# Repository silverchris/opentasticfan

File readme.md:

# OpentasticFan
OpentasticFan is a replacement for the factory control board found in most Fantastic Fans. It should also be possible to upgrade a basic Fantastic Fan that does not have rain sensing or power opening with the addition of a [Fantastic Fan lift motor assembly](https://www.etrailer.com/Accessories-and-Parts/Fantastic-Vent/FVK6010-80.html).

It supports:
- Cover Opening and Closing
- Rain Sensing
- Fan Speed Control 
- OLED Display and Rotary Encoder for local control
- Remote control via [Home Assistant](https://www.home-assistant.io/)

## Hardware

- [SH1106 128x64 i2c OLED Display](https://www.amazon.ca/dp/B085RYPHT2)
- [Rotary Encoder with button](https://www.amazon.ca/WayinTop-Degree-Encoder-Development-Arduino/dp/B07T3672VK/)
- [Opentasticfan PCB](hardware/2.0)
- Optional Heated Capacitive Rain Sensor

## Software
Opentasticfan uses [ESPHome](https://esphome.io). Configuration is located at [config/2.0](config/2.0).

[Example configuration](config/2.0/example.yaml)

## OpentasticFan Installed

## OpentasticFan wiring

## OpentasticFan PCB

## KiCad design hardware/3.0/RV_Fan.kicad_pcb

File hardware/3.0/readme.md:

# OpentasticFan PCB 3.0

## Updates from 2.0
- Uses ESP32-S3 instead of classic ESP32 (U5)
- USB for programming intergrated (J9, R6, R8, D1)
- Uses DRV8874PWR(U1, U2) for both motor controls. Combined with the better ADC of the ESP32-S3 gives accurate current measurement.
- AMS1117(U3) instead of switch mode regulator for power supply to reduce BOM cost
- Changed from Dallas DS18B20 to NTC thermistor(TH1) for air temperature for both the reduced cost, and due to the flaky support in ESPHome
- Added i2c pullup resistors (R1, R2)

## Assembly Notes
- ESP32-S3-WROOM-1 used, due to poor ADC on the classic ESP32. It is not availible for JLCPCB "Economic PCB Assembly" and will need to be hand soldered.
- Most SMD parts are availible through LCSC/JLCPCB with "Economic PCB Assembly". If having JLCPCB do the SMD assembly, you will need to install/solder C5, J1, J2, J3, J4, J6, J7, J8, U5
- J5 doesn't need to be populated. It's currently unused.
- Install J1, J2, so the screw terminals face out from the PCB with mating connector installed.

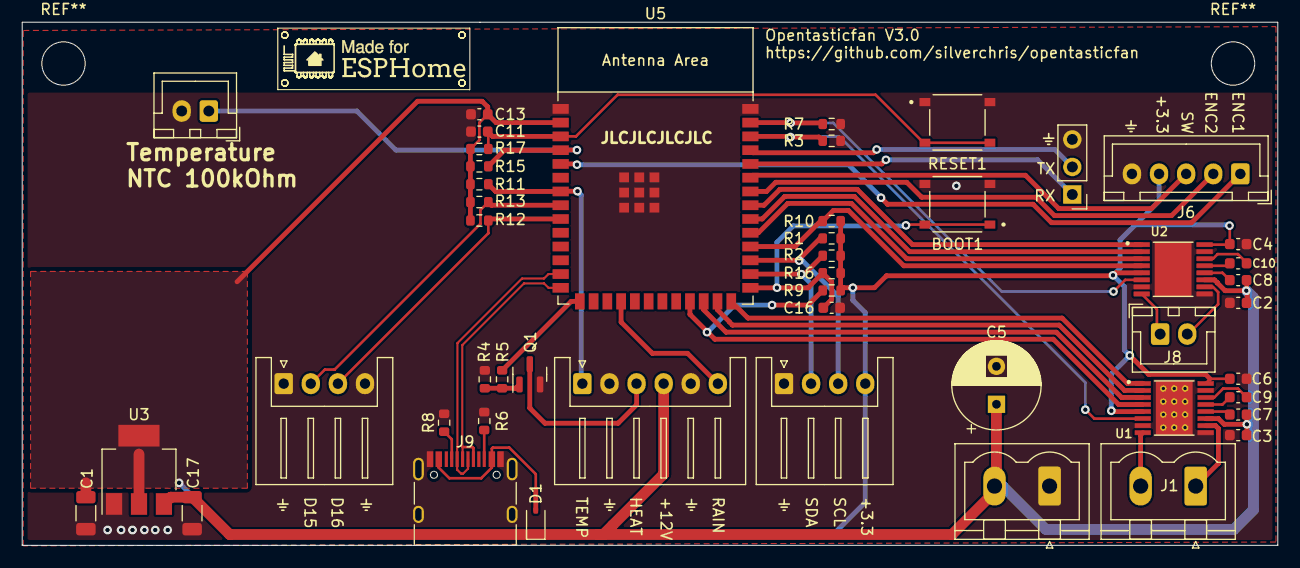
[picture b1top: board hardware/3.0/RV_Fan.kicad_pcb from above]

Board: 2 copper layers, 115.8 x 48.3 mm, 48 parts (0 on the bottom side), 45 nets.

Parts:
BOOT1: TS-1187A-B-A-B; button
C1: 22uF; C_1206_3216Metric
C2, C3, C4, C6, C7, C8, C11, C13, C16: 0.1uF; C_0603_1608Metric
C5: 220uF; CP_Radial_D8.0mm_P3.50mm
C9, C10: 22nF; C_0603_1608Metric
C17: 4.7uF; C_1206_3216Metric
D1: 1N5819WS; D_SOD-323
J1: FAN; PhoenixContact_MSTBVA_2,5_2-G-5,08_1x02_P5.08mm_Vertical
J2: PhoenixContact_MSTBVA_2,5_2-G-5,08_1x02_P5.08mm_Vertical
J3: JST_XH_S6B-XH-A_1x06_P2.50mm_Horizontal
J4, J5: JST_XH_S4B-XH-A_1x04_P2.50mm_Horizontal
J6: JST_XH_B5B-XH-A_1x05_P2.50mm_Vertical
J7: PinHeader_1x03_P2.54mm_Vertical
J8: COVER; JST_XH_B2B-XH-A_1x02_P2.50mm_Vertical
J9: USB_C_Receptacle_USB2.0; USB_C_Receptacle_HRO_TYPE-C-31-M-12
Q1: AO3400A; SOT-23
R1, R2, R4, R9, R10, R12, R13, R16, R17: 10k; R_0603_1608Metric
R3: 1.5k; R_0603_1608Metric
R5: 100; R_0603_1608Metric
R6, R8: 5.1k; R_0603_1608Metric
R7: 24k; R_0603_1608Metric
R11, R15: 51k; R_0603_1608Metric
RESET1: TS-1187A-B-A-B; button
TH1: 100k; JST_XH_B2B-XH-A_1x02_P2.50mm_Vertical
U1, U2: DRV8874PWPR; IC_DRV8876PWPT
U3: AMS1117-3.3; SOT-223-3_TabPin2
U5: ESP32-S3-WROOM-1

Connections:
+3.3V: C1.1, C4.1, C6.1, C13.1, J4.4, J6.4, R1.1, R2.1, R9.1, R10.1, R11.1, R12.1, R13.1, R15.1, R16.1, R17.1, U1.5 (VREF), U1.16 (PMODE), U2.5 (VREF), U2.16 (PMODE), U3.2 (VO), U5.2 (3V3)
+12V: C2.1, C3.1, C5.1, C7.1, C8.1, C17.1, D1.1 (K), J2.2, J3.4, U1.11 (VM), U2.11 (VM), U3.3 (VI)
/BOOT: BOOT1.1, C16.1, R16.2, U5.27 (GPIO0/BOOT)
/DEW_HEATER: R5.2, U5.15 (GPIO3/TOUCH3/ADC1_CH2)
/DEW_HEATER_OUT: J3.3, Q1.3 (D)
/DEW_TEMP: J3.1, R11.2, U5.7 (GPIO7/TOUCH7/ADC1_CH6)
/D_IN1: J5.3, R12.2, U5.9 (GPIO16/U0CTS/ADC2_CH5/XTAL_32K_N)
/D_IN2: J5.2, R13.2, U5.8 (GPIO15/U0RTS/ADC2_CH4/XTAL_32K_P)
/EN: C11.1, R17.2, RESET1.2, U5.3 (EN)
/ENC1: J6.1, U5.5 (GPIO5/TOUCH5/ADC1_CH4)
/ENC2: J6.2, U5.34 (MTDI/GPIO41/CLK_OUT1)
/RAIN: J3.6, U5.18 (GPIO10/TOUCH10/ADC1_CH9/FSPICS0/FSPIIO4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)
/RX: J7.1, U5.36 (U0RXD/GPIO44/CLK_OUT2)
/SCL: J4.3, R1.2, U5.29 (SPIIO7/GPIO36/FSPICLK/SUBSPICLK)
/SDA: J4.2, R2.2, U5.28 (SPIIO6/GPIO35/FSPID/SUBSPID)
/SW: J6.3, U5.35 (MTMS/GPIO42)
/TEMP: R15.2, TH1.1, U5.4 (GPIO4/TOUCH4/ADC1_CH3)
/TX: J7.2, U5.37 (U0TXD/GPIO43/CLK_OUT1)
/USB_D+: J9.A6 (D+), J9.B6 (D+), U5.14 (GPIO20/U1CTS/ADC2_CH9/CLK_OUT1/USB_D+)
/USB_D-: J9.A7 (D-), J9.B7 (D-), U5.13 (GPIO19/U1RTS/ADC2_CH8/CLK_OUT2/USB_D-)
/USB_VBUS: D1.2 (A), J9.A4 (VBUS), J9.A9 (VBUS), J9.B4 (VBUS), J9.B9 (VBUS)
GND: BOOT1.2, C1.2, C2.2, C3.2, C4.2, C5.2, C6.2, C11.2, C13.2, C16.2, C17.2, J2.1, J3.2, J3.5, J4.1, J5.1, J5.4, J6.5, J7.3, J9.A1 (GND), J9.A12 (GND), J9.B1 (GND), J9.B12 (GND), J9.S1 (SHIELD), Q1.2 (S), R3.2, R4.2, R6.2, R7.2, R8.2, RESET1.1, TH1.2, U1.7 (IMODE), U1.9 (PGND), U1.15 (GND), U1.17 (EXP), U1.18 (EXP), U1.19 (EXP), U1.20 (EXP), U1.21 (EXP), U1.22 (EXP), U1.23 (EXP), U1.24 (EXP), U1.25 (EXP), U1.26 (EXP), U1.27 (EXP), U1.28 (EXP), U1.29 (EXP), U2.7 (IMODE), U2.9 (PGND), U2.15 (GND), U2.17 (EXP), U3.1 (GND), U5.1 (GND), U5.40 (GND), U5.41 (GND)
unnamed: J1.1, U1.10 (OUT2)
unnamed: J1.2, U1.8 (OUT1)
unnamed: J8.1, U2.8 (OUT1)
unnamed: J8.2, U2.10 (OUT2)
unnamed: J9.A5 (CC1), R8.1
unnamed: J9.B5 (CC2), R6.1
unnamed: Q1.1 (G), R4.1, R5.1
unnamed: C9.1, U1.13 (CPH)
unnamed: C9.2, U1.14 (CPL)
unnamed: C7.2, U1.12 (VCP)
unnamed: C10.1, U2.13 (CPH)
unnamed: C10.2, U2.14 (CPL)
unnamed: C8.2, U2.12 (VCP)
U1_IN1: U1.1 (EN/IN1), U5.26 (GPIO45)
U1_IN2: U1.2 (PH/IN2), U5.25 (GPIO48/SPICLK_N/SUBSPICLK_N_DIFF)
U1_Isense: R3.1, U1.6 (IPROPI), U5.38 (GPIO2/TOUCH2/ADC1_CH1)
U2_IN1: U2.1 (EN/IN1), U5.33 (MTDO/GPIO40/CLK_OUT2)
U2_IN2: U2.2 (PH/IN2), U5.32 (MTCK/GPIO39/CLK_OUT3/SUBSPICS1)
U2_Isense: R7.1, U2.6 (IPROPI), U5.39 (GPIO1/TOUCH1/ADC1_CH0)
~U1_FAULT: R9.2, U1.4 (~NFAULT), U5.23 (GPIO21)
~U1_SLEEP: U1.3 (NSLEEP), U5.24 (GPIO47/SPICLK_P/SUBSPICLK_P_DIFF)
~U2_FAULT: R10.2, U2.4 (~NFAULT), U5.30 (SPIDQS/GPIO37/FSPIQ/SUBSPIQ)
~U2_SLEEP: U2.3 (NSLEEP), U5.31 (GPIO38/FSPIWP/SUBSPIWP)

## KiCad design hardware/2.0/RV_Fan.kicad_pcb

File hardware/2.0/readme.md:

# OpentasticFan PCB

## Assembly Notes
- ESP32-SOLO-1 used on prototypes, for reduced JLCPCB assembly costs.
- All SMD parts are availible through LCSC/JLCPCB with "Economic PCB Assembly". If having JLCPCB do the SMD assembly, you will need to install/solder C5, U5, J1, J2, J3, J4, J6, J10
- If using a NTC thermistor instead of a DS18B20, change R15 to correct value for thermistor
- Recommend using JST XH headers for J3, J4, J6. They fit on this revision, but tightly.
- J5 doesn't need to be populated. It's currently unused.
- Install J1, J2, J10 so the screw terminals face out from the PCB with mating connector installed.

## Future Design changes
- Use ams1117 instead of switch mode regulator to reduce BOM costs/simplify.
- Replace .1" Headers with JST Connectors, for vibration resistance.
- Possibly replace DRV8874 with A4950E. This will likely result in needing to use a op-amp/current sense amplifier to monitor fan current?

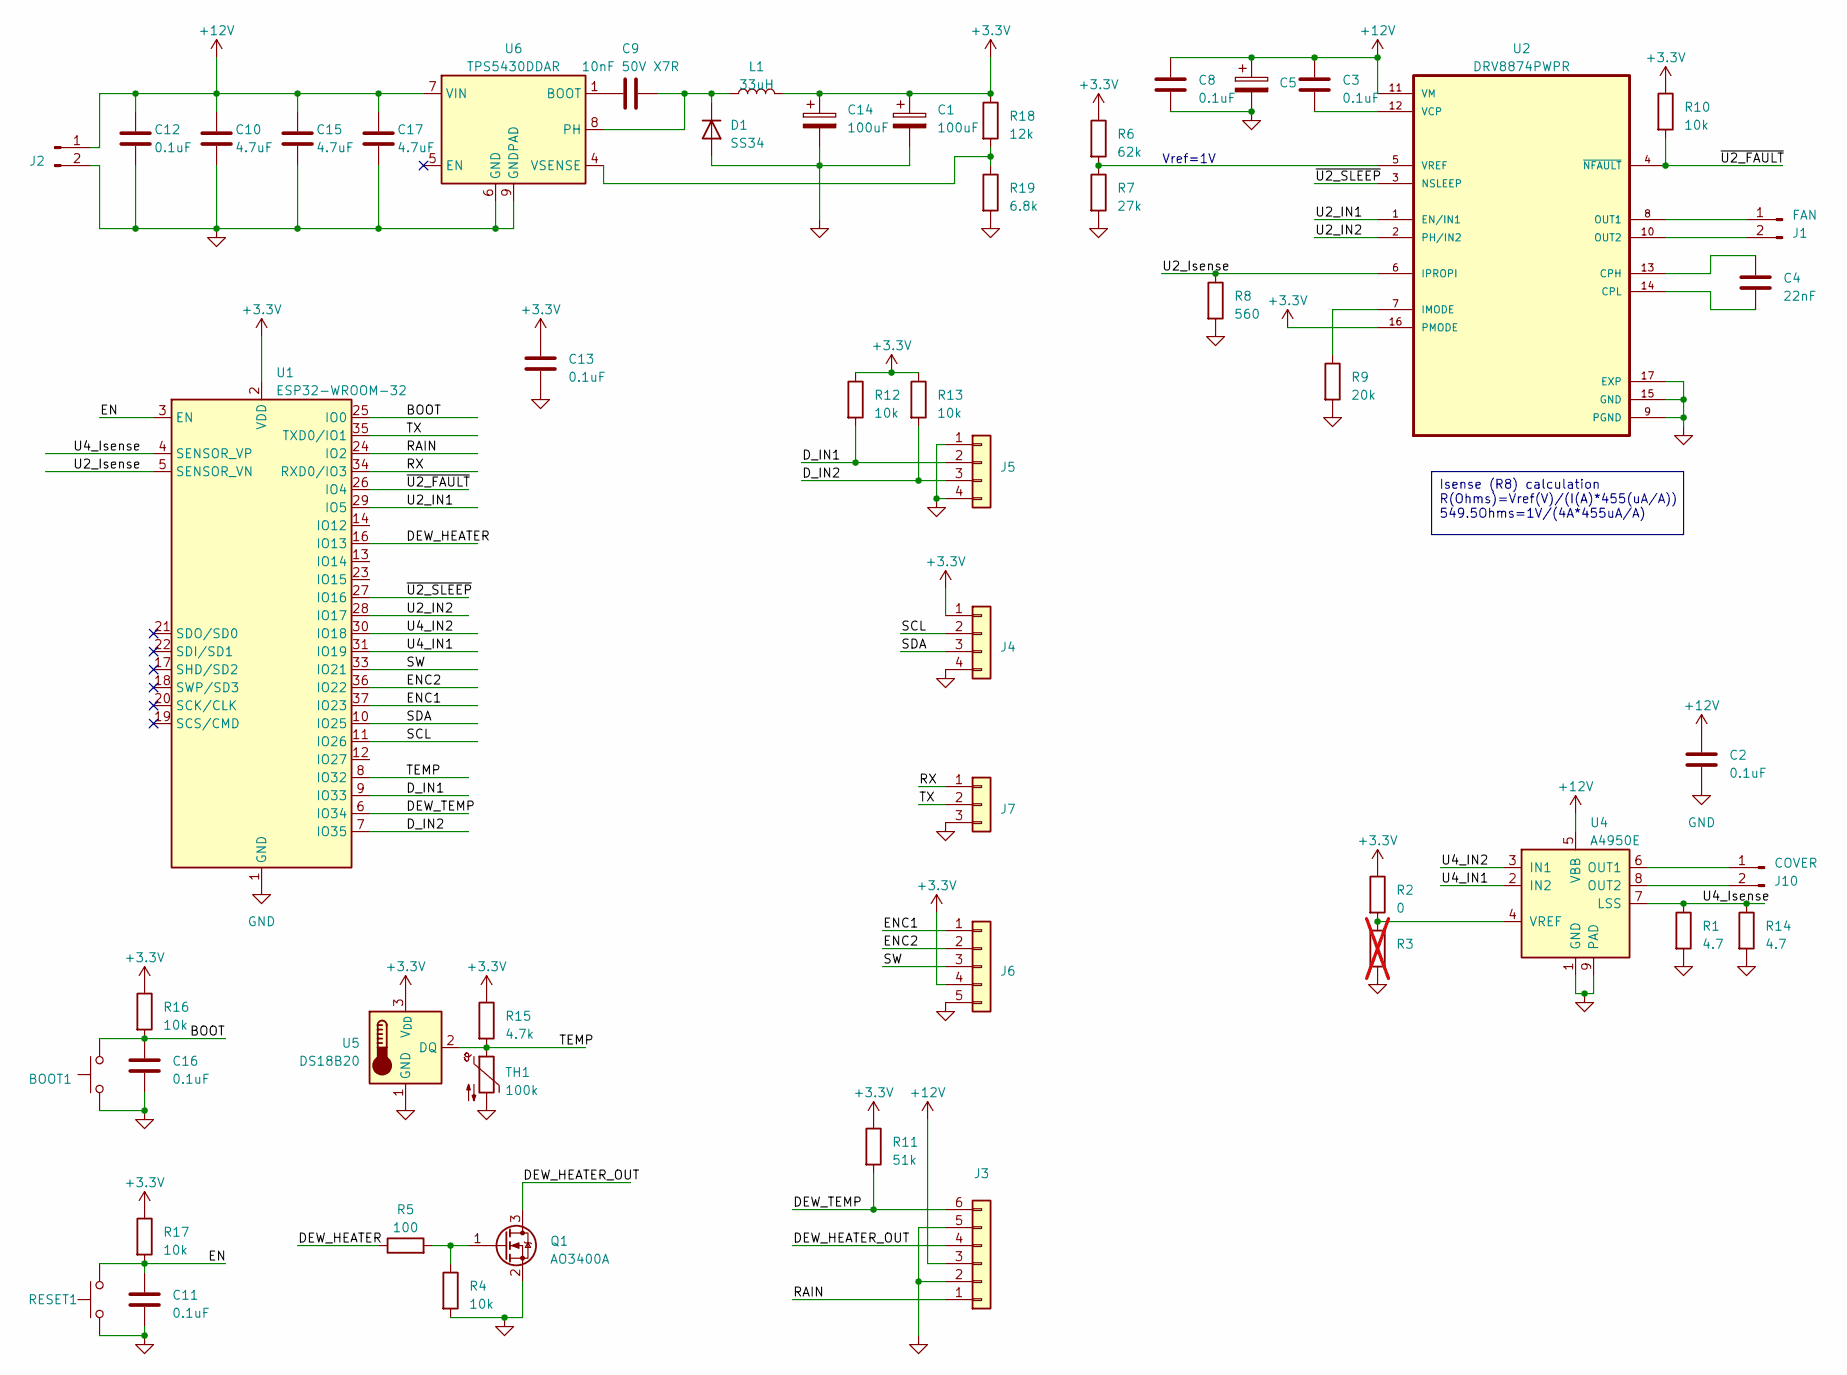
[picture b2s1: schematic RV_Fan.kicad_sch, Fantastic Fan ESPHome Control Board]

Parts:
BOOT1: TS-1187A-B-A-B; button
C1: 100uF; C_1206_3216Metric
C2, C3, C8, C11, C12, C13, C16: 0.1uF; C_0603_1608Metric
C4: 22nF; C_0603_1608Metric; LCSC Part # C21122
C5: CP_Radial_D8.0mm_P3.50mm
C9: 10nF 50V X7R; C_0603_1608Metric
C10, C15, C17: 4.7uF; C_1206_3216Metric; LCSC Part # C29823
C14: 100uF; C_1206_3216Metric; LCSC Part # C15008
D1: SS34; D_SMA
J1: FAN; PhoenixContact_MSTBVA_2,5_2-G-5,08_1x02_P5.08mm_Vertical
J2: PhoenixContact_MSTBVA_2,5_2-G-5,08_1x02_P5.08mm_Vertical
J3: PinHeader_1x06_P2.54mm_Horizontal
J4, J5: PinHeader_1x04_P2.54mm_Horizontal
J6: PinHeader_1x05_P2.54mm_Vertical
J7: PinHeader_1x03_P2.54mm_Vertical
J10: COVER; PhoenixContact_MSTBVA_2,5_2-G-5,08_1x02_P5.08mm_Vertical
L1: 33uH; 1255AY100MP3; LCSC Part # C1332315
Q1: AO3400A; SOT-23
R1, R14: 4.7; R_0805_2012Metric; LCSC Part # C17675
R2: 0; R_0603_1608Metric
R3: R_0603_1608Metric; not fitted
R4, R10, R12, R13, R16, R17: 10k; R_0603_1608Metric
R5: 100; R_0603_1608Metric
R6: 62k; R_0603_1608Metric
R7: 27k; R_0603_1608Metric
R8: 560; R_0603_1608Metric
R9: 20k; R_0603_1608Metric
R11: 51k; R_0603_1608Metric; LCSC Part # C23196
R15: 4.7k; R_0603_1608Metric
R18: 12k; R_0603_1608Metric
R19: 6.8k; R_0603_1608Metric
RESET1: TS-1187A-B-A-B; button
TH1: 100k; PinHeader_1x02_P2.54mm_Vertical
U1: ESP32-WROOM-32
U2: DRV8874PWPR; IC_DRV8876PWPT; PARTREV E; LCSC Part # C1855818
U4: A4950E; SOIC-8-1EP_3.9x4.9mm_P1.27mm_EP2.41x3.3mm
U5: DS18B20; TO-92_Inline
U6: TPS5430DDAR; TI_SO-PowerPAD-8_ThermalVias

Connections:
+3.3V: C1.1, C13.1, C14.1, J4.1, J6.4, L1.2, R2.1, R6.1, R10.1, R11.1, R12.1, R13.1, R15.1, R16.1, R17.1, R18.1, U1.2 (VDD), U2.16 (PMODE), U5.3 (V_{DD})
+12V: C2.1, C3.1, C5.1, C8.1, C10.1, C12.1, C15.1, C17.1, J2.1, J3.3, U2.11 (VM), U4.5 (VBB), U6.7 (VIN)
/BOOT: BOOT1.1, C16.1, R16.2, U1.25 (IO0)
/DEW_HEATER: R5.1, U1.16 (IO13)
/DEW_HEATER_OUT: J3.4, Q1.3 (D)
/DEW_TEMP: J3.6, R11.2, U1.6 (IO34)
/D_IN1: J5.2, R12.2, U1.9 (IO33)
/D_IN2: J5.3, R13.2, U1.7 (IO35)
/EN: C11.1, R17.2, RESET1.2, U1.3 (EN)
/ENC1: J6.1, U1.37 (IO23)
/ENC2: J6.2, U1.36 (IO22)
/RAIN: J3.1, U1.24 (IO2)
/RX: J7.1, U1.34 (RXD0/IO3)
/SCL: J4.2, U1.11 (IO26)
/SDA: J4.3, U1.10 (IO25)
/SW: J6.3, U1.33 (IO21)
/TEMP: R15.2, TH1.1, U1.8 (IO32), U5.2 (DQ)
/TX: J7.2, U1.35 (TXD0/IO1)
/U2_IN1: U1.29 (IO5), U2.1 (EN/IN1)
/U2_IN2: U1.28 (IO17), U2.2 (PH/IN2)
/U2_Isense: R8.1, U1.5 (SENSOR_VN), U2.6 (IPROPI)
/U4_IN1: U1.31 (IO19), U4.2 (IN2)
/U4_IN2: U1.30 (IO18), U4.3 (IN1)
/U4_Isense: R1.1, R14.1, U1.4 (SENSOR_VP), U4.7 (LSS)
/~U2_FAULT: R10.2, U1.26 (IO4), U2.4 (~NFAULT)
/~U2_SLEEP: U1.27 (IO16), U2.3 (NSLEEP)
GND: BOOT1.2, C1.2, C2.2, C5.2, C8.2, C10.2, C11.2, C12.2, C13.2, C14.2, C15.2, C16.2, C17.2, D1.2 (A), J2.2, J3.2, J3.5, J4.4, J5.1, J5.4, J6.5, J7.3, Q1.2 (S), R1.2, R3.2, R4.2, R7.2, R8.2, R9.2, R14.2, R19.2, RESET1.1, TH1.2, U1.1 (GND), U1.15 (GND), U1.38 (GND), U1.39 (GND), U2.9 (PGND), U2.15 (GND), U2.17 (EXP), U4.1 (GND), U4.9 (PAD), U5.1 (GND), U6.6 (GND), U6.9 (GNDPAD)
unnamed: C9.2, D1.1 (K), L1.1, U6.8 (PH)
unnamed: J1.1, U2.8 (OUT1)
unnamed: J1.2, U2.10 (OUT2)
unnamed: J10.1, U4.6 (OUT1)
unnamed: J10.2, U4.8 (OUT2)
unnamed: Q1.1 (G), R4.1, R5.2
unnamed: C4.1, U2.13 (CPH)
unnamed: C4.2, U2.14 (CPL)
unnamed: R9.1, U2.7 (IMODE)
unnamed: C3.2, U2.12 (VCP)
unnamed: R6.2, R7.1, U2.5 (VREF)
unnamed: R2.2, R3.1, U4.4 (VREF)
unnamed: C9.1, U6.1 (BOOT)
unnamed: R18.2, R19.1, U6.4 (VSENSE)

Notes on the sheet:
Isense (R8) calculation R(Ohms)=Vref(V)/(I(A)*455(uA/A)) 549.5Ohms=1V/(4A*455uA/A)
Vref=1V

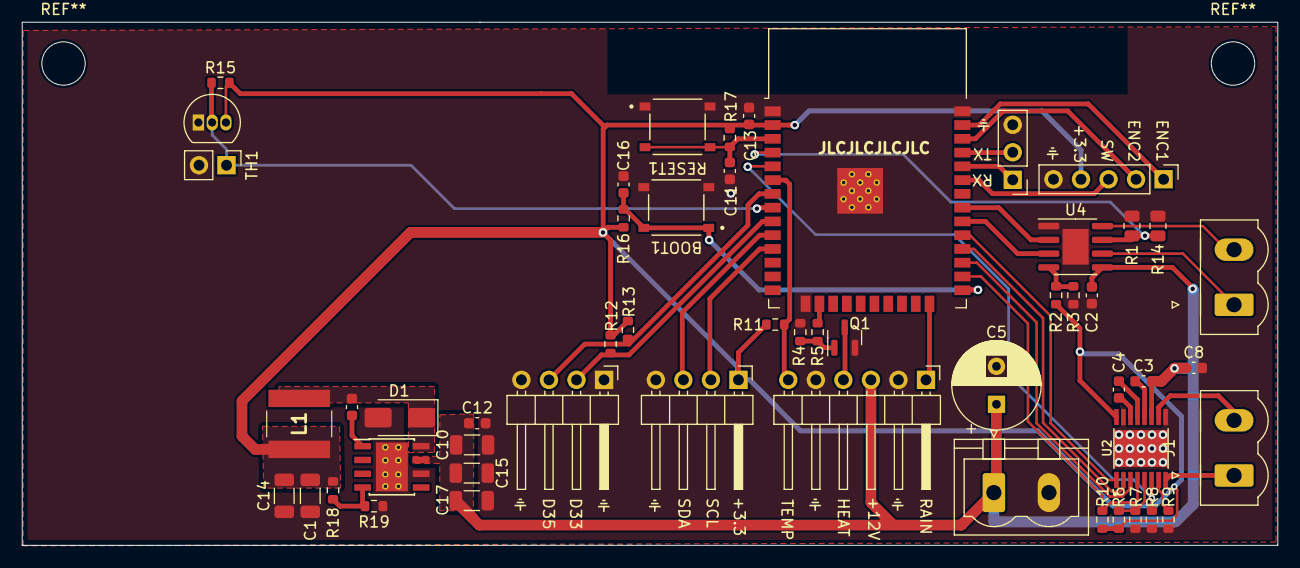
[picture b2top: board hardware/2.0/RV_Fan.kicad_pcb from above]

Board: 2 copper layers, 115.8 x 48.3 mm, 53 parts (0 on the bottom side), 41 nets.

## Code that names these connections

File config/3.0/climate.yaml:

substitutions:
  temperature_sensor: local_temperature
  motor_enable_pin: GPIO47
  motor_forward_pin: GPIO45
  motor_reverse_pin: GPIO48
  motor_error_pin: GPIO21
  motor_current_pin: GPIO2

power_supply:
  - id: "motor_enable"
    pin: ${motor_enable_pin}

output:
  - platform: ledc
    id: motor_forward_pin
    frequency: 32kHz
    pin: ${motor_forward_pin}
    max_power: 0.99
    min_power: 0.40
    zero_means_zero: true
    power_supply: motor_enable
  - platform: ledc
    id: motor_reverse_pin
    pin: ${motor_reverse_pin}
    frequency: 32kHz
    max_power: 0.99
    min_power: 0.40
    zero_means_zero: true
    power_supply: motor_enable
  #Template Output for climate component, so only the enabled component can write to the motor output, and direction
  - platform: template
    id: climate_output
    type: float
    write_action:
      - if:
          condition:
            - lambda: |-
                return id(fan_mode).state == "AUTO";
          then:
            if:
              condition:
                - lambda: |-
                    return id(fan_direction).state == "OUT";
              then:
                - output.set_level:
                    id: motor_forward_pin
                    level: !lambda return state;
              else:
                - output.set_level:
                    id: motor_reverse_pin
                    level: !lambda return state;
  #Template Output for fan component, so only the enabled component can write to the motor output, and direction
  - platform: template
    id: fan_output
    type: float
    write_action:
      - if:
          condition:
            - lambda: |-
                return id(fan_mode).state == "MANUAL";
          then:
            if:
              condition:
                - lambda: |-
                    return id(fan_direction).state == "OUT";
              then:
                - output.set_level:
                    id: motor_forward_pin
                    level: !lambda return state;
              else:
                - output.set_level:
                    id: motor_reverse_pin
                    level: !lambda return state;

fan:
  - platform: speed
    id: my_fan
    name: "Fan"
    output: fan_output
    on_turn_on:
      - climate.control:
          id: fan_climate
          mode: "OFF"

climate:
  - platform: pid
    name: "PID Climate Controller"
    id: fan_climate
    sensor: ${temperature_sensor}
    default_target_temperature: 21°C
    cool_output: climate_output
    control_parameters:
      kp: 1
      ki: 3
      kd: 0.2
    deadband_parameters:
      threshold_high: 0.5
      threshold_low: 0.5

select:
  - platform: template
    name: "Mode"
    id: fan_mode
    optimistic: true
    restore_value: true
    options:
      - MANUAL
      - AUTO
    initial_option: AUTO
    set_action:
      if:
        condition:
          - lambda: |-
              return id(fan_mode).state == "MANUAL";
        then:
          - climate.control:
              id: fan_climate
              mode: "OFF"
        else:
          - fan.turn_off: my_fan
  - platform: template
    name: "Direction"
    id: fan_direction
    optimistic: true
    restore_value: true
    options:
      - IN
      - OUT
    initial_option: OUT
    set_action:
      if:
        condition:
          - lambda: |-
              return id(fan_direction).state == "OUT";
        then:
          - output.set_level:
              id: motor_forward_pin
              level: 0
          - if:
              condition:
                fan.is_on: my_fan
              then:
                - fan.turn_off: my_fan
                - delay: 2s
                - fan.turn_on: my_fan

        else:
          - output.set_level:
              id: motor_reverse_pin
              level: 0
          - if:
              condition:
                fan.is_on: my_fan
              then:
                - fan.turn_off: my_fan
                - delay: 2s
                - fan.turn_on: my_fan

binary_sensor:
  - platform: gpio
    pin:
      number: ${motor_error_pin}
      inverted: true
    name: "Motor Fault"
    filters:
      - delayed_on: 1s

sensor:
  - platform: adc
    pin: ${motor_current_pin}
    update_interval: 1s
    attenuation: 11db
    id: motor_current
    name: Fan Current
    filters:
      - lambda: return (x/1500)/0.000455;
      - quantile:
          window_size: 5
          send_every: 5
          send_first_at: 5
    unit_of_measurement: "A"

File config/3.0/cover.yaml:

substitutions:
  endstop_current: "120" #Sets the current threshold in mA that turns the endstops on
  cover_open_pin: GPIO40
  cover_close_pin: GPIO39
  cover_current_pin: GPIO1
  cover_enable_pin: GPIO38

output:
  - platform: gpio
    pin: ${cover_close_pin}
    id: cover_close
  - platform: gpio
    pin: ${cover_open_pin}
    id: cover_open
  - platform: gpio
    pin: ${cover_enable_pin}
    id: cover_enable

sensor:
  - platform: adc
    pin: ${cover_current_pin}
    update_interval: .1s
    attenuation: 11db
    id: cover_current
    internal: true
    filters:
      - lambda: return ((x/24000)/0.000455)*1000;
      - quantile:
          window_size: 5
          send_every: 5
          send_first_at: 5
      # - median:
      #     window_size: 5
      #     send_every: 5
      #     send_first_at: 5
    unit_of_measurement: "mA"

binary_sensor:
  - platform: analog_threshold
    name: "Cover Close Endstop"
    sensor_id: cover_current
    threshold: ${endstop_current}
    id: cover_close_endstop
    filters:
      - lambda: if(id(vent_lid).current_operation == CoverOperation::COVER_OPERATION_CLOSING) {return x;} else {return false;}
      - delayed_on: 3s
    internal: true
  - platform: analog_threshold
    name: "Cover Open Endstop"
    sensor_id: cover_current
    threshold: ${endstop_current}
    id: cover_open_endstop
    filters:
      - lambda: if(id(vent_lid).current_operation == CoverOperation::COVER_OPERATION_OPENING) {return x;} else {return false;}
      - delayed_on: 3s
    internal: true

cover:
  - platform: endstop
    name: "Cover"
    id: vent_lid
    open_action:
      - output.turn_on: cover_enable
      - output.turn_on: cover_open
      - select.set:
          id: close_reason
          option: "NONE"
    open_duration: 12s
    open_endstop: cover_open_endstop
    close_action:
      - output.turn_on: cover_enable
      - output.turn_on: cover_close
    close_duration: 12s
    close_endstop: cover_close_endstop
    stop_action:
      - output.turn_off: cover_open
      - output.turn_off: cover_close
      - output.turn_off: cover_enable
    max_duration: 30s

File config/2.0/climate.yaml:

substitutions:
  temperature_sensor: local_temperature
  motor_enable_pin: GPIO16
  motor_forward_pin: GPIO5
  motor_reverse_pin: GPIO17
  motor_error_pin: GPIO4
  motor_current_pin: GPIO39

power_supply:
  - id: "motor_enable"
    pin: ${motor_enable_pin}

output:
  - platform: ledc
    id: motor_forward_pin
    frequency: 32kHz
    pin: ${motor_forward_pin}
    max_power: 0.99
    min_power: 0.40
    zero_means_zero: true
    power_supply: motor_enable
  - platform: ledc
    id: motor_reverse_pin
    pin: ${motor_reverse_pin}
    frequency: 32kHz
    max_power: 0.99
    min_power: 0.40
    zero_means_zero: true
    power_supply: motor_enable
  #Template Output for climate component, so only the enabled component can write to the motor output, and direction
  - platform: template
    id: climate_output
    type: float
    write_action:
      - if:
          condition:
            - lambda: |-
                return id(fan_mode).state == "AUTO";
          then:
            if:
              condition:
                - lambda: |-
                    return id(fan_direction).state == "OUT";
              then:
                - output.set_level:
                    id: motor_forward_pin
                    level: !lambda return state;
              else:
                - output.set_level:
                    id: motor_reverse_pin
                    level: !lambda return state;
  #Template Output for fan component, so only the enabled component can write to the motor output, and direction
  - platform: template
    id: fan_output
    type: float
    write_action:
      - if:
          condition:
            - lambda: |-
                return id(fan_mode).state == "MANUAL";
          then:
            if:
              condition:
                - lambda: |-
                    return id(fan_direction).state == "OUT";
              then:
                - output.set_level:
                    id: motor_forward_pin
                    level: !lambda return state;
              else:
                - output.set_level:
                    id: motor_reverse_pin
                    level: !lambda return state;

fan:
  - platform: speed
    id: my_fan
    name: "Fan"
    output: fan_output
    on_turn_on:
      - climate.control:
          id: fan_climate
          mode: "OFF"

climate:
  - platform: pid
    name: "PID Climate Controller"
    id: fan_climate
    sensor: ${temperature_sensor}
    default_target_temperature: 21°C
    cool_output: climate_output
    control_parameters:
      kp: 1
      ki: 3
      kd: 0.2
    deadband_parameters:
      threshold_high: 0.5
      threshold_low: 0.5

select:
  - platform: template
    name: "Mode"
    id: fan_mode
    optimistic: true
    restore_value: true
    options:
      - MANUAL
      - AUTO
    initial_option: AUTO
    set_action:
      if:
        condition:
          - lambda: |-
              return id(fan_mode).state == "MANUAL";
        then:
          - climate.control:
              id: fan_climate
              mode: "OFF"
        else:
          - fan.turn_off: my_fan
  - platform: template
    name: "Direction"
    id: fan_direction
    optimistic: true
    restore_value: true
    options:
      - IN
      - OUT
    initial_option: OUT
    set_action:
      if:
        condition:
          - lambda: |-
              return id(fan_direction).state == "OUT";
        then:
          - output.set_level:
              id: motor_forward_pin
              level: 0
          - if:
              condition:
                fan.is_on: my_fan
              then:
                - fan.turn_off: my_fan
                - delay: 2s
                - fan.turn_on: my_fan

        else:
          - output.set_level:
              id: motor_reverse_pin
              level: 0
          - if:
              condition:
                fan.is_on: my_fan
              then:
                - fan.turn_off: my_fan
                - delay: 2s
                - fan.turn_on: my_fan

binary_sensor:
  - platform: gpio
    pin:
      number: ${motor_error_pin}
      inverted: true
    name: "Motor Fault"
    filters:
      - delayed_on: 1s

sensor:
  - platform: adc
    pin: ${motor_current_pin}
    update_interval: 1s
    attenuation: 0db
    id: motor_current
    name: Fan Current
    filters:
      - lambda: if(x>0.076){return (x/549.5)/0.000455;} else {return 0;} #ADC seems to have a minimum reading of 0.075V
      - quantile:
          window_size: 5
          send_every: 5
          send_first_at: 5
    unit_of_measurement: "A"

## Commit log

2023-08-16 Move to subfolder
2023-08-16 Remove duplicated files
2023-08-16 added readme
2023-08-16 Added hardware
2023-08-17 Readme updates
2023-08-17 Add hardware readme
2023-10-12 Add version 3.0
2023-10-12 example fixups
2024-06-08 remove unneeded external_components
2024-06-20 Enable sensor heater
2024-06-21 Increase rain sensor heater temperature
